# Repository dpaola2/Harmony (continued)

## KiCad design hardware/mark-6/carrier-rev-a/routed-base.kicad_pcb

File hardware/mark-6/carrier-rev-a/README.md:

# Harmony Mark-6 carrier, revision A

Current logistics, September 26: core modules are received, and the revision B shells, LCD supports and carrier gauge passed loose fit checks. Screws and foam are ordered. The SD trial playlist is prepared. The assembled carrier remains unordered. A [supplier quote request](supplier-quote-notes.md) was sent to PCBWay for DFM review and pricing; the response is pending. Physical mating, cable mapping and powered qualification remain open. The historical design record below retains its original dated assumptions.

September 22 display update: **Waveshare 29318 (ST7796S)** replaces unavailable Adafruit #5846. [PiShop.us](https://www.pishop.us/product/3-5inch-capacitive-touch-display-320-480-ips-2tpd/) lists it in stock at $24.95. The [sourcing and compatibility review](display-sourcing.md), [hollow prototype](../../../enclosure/mark-6/fit-prototype/README.md) and [firmware](../../../firmware/mark-6/feather-carrier/README.md) now use this module. The carrier electrical nets are unchanged. Manufacturing remains review-only.

Updated September 22, 2026. HARMONY-17. **Routed prototype design; manufacturing review package, not an order release.**

Dave printed and accepted the **74 x 178 x 28 mm** size dummy. The component
stack now uses the actual Feather and ANO 3D models, specified sockets and
an antenna cutout. The routed four-layer PCB passes KiCad DRC with **zero
violations and zero unconnected nets**. The independent PCB audit matches
122 electrical pads to the schematic and all 28 Feather mating coordinates
to vendor CAD. The schematic also passes ERC.

The [assembly readiness review](assembly-readiness.md) records the corrected ENIG metadata, part/placement audit and the documented U1 thermal-hole DRC warning.

Start with [the design review](output/pdf/design-review.pdf),
[editable PCB](harmony-mark6-carrier.kicad_pcb),
[schematic](harmony-mark6-carrier.kicad_sch), and
[manufacturing review package](output/manufacturing-review/README.md).
[Mechanical review](mechanical-review.md), [power review](power-review.md)
and [machine-readable verification](pcb-verification.json) document the
checks and their limits. No order has been placed.

USB-only operation remains adopted. Battery space is reserved for Mark 8.
The accepted size dummy proves the outside dimensions work for Dave; physical
display fit, header insertion and cable access still require a trial assembly.
The revised prototype uses the Waveshare vendor STEP, including rear connectors.

Dave adopted a 3.5-inch display and separate display/storage buses. The carrier
will arrive assembled, including its sockets and connectors. Dave plugs in a
factory-headered ESP32 Feather V2 (#5900), a display ribbon cable and the
controls cable. No hand soldering is part of the intended assembly.

## Parts and interfaces

Bluetooth verification: the live DigiKey cart contains four Adafruit #5900,
DigiKey 1528-5900-ND. Adafruit's Feather V2 schematic identifies X3 as
ESP32-PICO-MINI-02, containing ESP32-PICO-V3-02. This original ESP32 supports
Bluetooth 4.2 BR/EDR (Classic) and BLE; it meets the radio requirement for
A2DP source streaming. Adafruit #5900 explicitly specifies Classic/LE, and
[Espressif's module datasheet](https://documentation.espressif.com/esp32-pico-mini-02_datasheet_en.html)
confirms BR/EDR. [ESP-IDF's A2DP source example](https://docs.espressif.com/projects/esp-idf/en/stable/esp32/api-reference/bluetooth/esp_a2dp.html)
documents audio transmission. This verifies specifications, not a physical
playback test on the new Feather. Keep this exact Classic-capable model in
the BOM; a BLE-only ESP32-family substitution does not satisfy the requirement.

| Function | Draft implementation | Status |
| --- | --- | --- |
| Processor and Bluetooth | Adafruit ESP32 Feather V2 #5900 in carrier sockets | Four in DigiKey cart; not purchased |
| Display | Waveshare 29318 3.5-inch IPS, via 18-pin ribbon | Glass 61.00 x 92.44 mm; PiShop.us lists in stock |
| Storage | Hirose DM3AT-SF-PEJM5 microSD socket on carrier | Pin and footprint pad sets checked |
| Controls | Previously ordered assembled ANO I2C control board | 50 mm QT-to-QT cable; nominal stack checked |
| Power | USB-C through Feather; TPS62162 3.3 V peripheral supply | USB budget reviewed; physical startup/load/thermal qualification remains |

The EYESPI breakout replaces the proposed FeatherWing connection so that the
carrier can assign display and storage to separate SPI hosts. Its onboard SD
socket stays unused. Capacitive touch on Waveshare 29318 is incidental; the interface
still uses physical controls.

## Proposed GPIO assignment

These are **ESP32 GPIO numbers**, not generic Feather pin numbers. Header
references below use the numbering in Adafruit's Feather V2 Eagle files.
They are for schematic development, not a breadboard wiring instruction.

| Signal | GPIO | Feather header | Destination |
| --- | ---: | --- | --- |
| SD clock | 5 | JP1.6 | Carrier SD CLK |
| SD MOSI | 19 | JP1.5 | Carrier SD CMD |
| SD MISO | 21 | JP1.4 | Carrier SD DAT0 |
| SD select | 25 | JP1.11 | Carrier SD DAT3 |
| Display clock | 14 | JP3.10 | EYESPI 4 |
| Display MOSI | 27 | JP3.6 | EYESPI 5 |
| Display select | 26 | JP1.12 | EYESPI 9 |
| Display command/data | 33 | JP3.7 | EYESPI 7 |
| Display reset | 32 | JP3.9 | EYESPI 8 |
| Display backlight control | 4 | JP1.7 | EYESPI 2 |
| Controls I2C clock | 20 | JP3.11 | Controls SCL |
| Controls I2C data | 22 | JP3.12 | Controls SDA |
| Peripheral power-good input | 34 | JP1.10 | TPS62162 PG |

Use SPI3 for SD and SPI2 for display in native ESP-IDF. The allocation does
not reuse signal GPIOs. A 47k pull-up reinforces GPIO5's normal high boot
strap; the SD clock destination is an input. GPIO12 and GPIO15 stay unused.
Display MISO and touch are unused. The display-side SD select is held high.
The Waveshare display uses SPI without jumper soldering. GPIO34 reads peripheral power-good before firmware starts I/O.

## Power, parts and mechanics

The exact carrier component choices are in `bom-draft.csv`; the grouped
assembler BOM is `output/manufacturing-review/assembly-bom.csv`. Both sockets
and every connector must be fitted by the assembler. F1 is a 0.75 A-hold
Bourns PTC, with 0.52 A hold at 60 C. The regulator uses 2.2 uH and 22 uF
input/output bulk capacitors. The [power review](power-review.md) gives the
source budget, limits and staged first-power procedure.

The [mechanical review](mechanical-review.md) records the 6.5 mm carrier
height, 12 mm ANO spacers, cable orientation and case-port requirements.
The vendor 3D model yields 0.88 mm nominal clearance above the Feather
beneath a 1.6 mm front wall. Display geometry uses the Waveshare vendor STEP.
The detailed assembly is in `output/mechanical/`; it is a review model,
not the final hollow housing.

The carrier cutout removes board material beneath the antenna. Ground pours
avoid the 15 mm halo, while unavoidable header copper remains inside part
of it. The finished device still needs an RF test. Vias inside SMT pads
require filled, copper-capped construction and assembler stencil review.
The release conditions are listed in the manufacturing package.

`build_pcb.py` creates the initial placement; `routing.ses` is the saved
routing result. `routed-base.kicad_pcb` preserves its imported state.
`finish_pcb.py` loads that base, completes the remaining routes, adjusts
edge clearance and fills ground planes. `verify_pcb.py` checks the final
board against the exported schematic netlist. Run it with KiCad's bundled
Python after generating a fresh `final-drc.json`.

## Evidence and limits

Mark-5 SD reads provoked clicks in its local VS1053 analog output; RAM-only
playback was clean. That did not establish shared SPI as the cause. Separate
buses reduce contention; they do not prove clean playback or replace power
layout work. Mark-6 must still demonstrate display refresh during Bluetooth
playback, controls, reconnection and the deferred full-album run.

Vendor Feather, display, ANO and EYESPI CAD, licenses and source hashes are
preserved in `reference/`. Passive socket symbols do not model the ESP32's
electrical limits, so a clean ERC alone cannot establish GPIO compatibility.
The netlist checks explicitly verify the connector mapping and supply
separation; bench and RF tests remain. The previous WROVER wiring is suspended
after two reported board failures; their root cause remains unknown.

## Sources and cross-references

- [Feather V2 vendor CAD](https://github.com/adafruit/Adafruit-ESP32-Feather-V2-PCB)
- [Selected Waveshare 29318 display](https://www.waveshare.com/3.5inch-capacitive-touch-lcd.htm)
- [EYESPI pinout](https://learn.adafruit.com/adafruit-eyespi-breakout-board/pinouts)
- [EYESPI vendor CAD](https://github.com/adafruit/Adafruit-EYESPI-PCB/tree/bc5fa13b55c25feb3bf47e483b4d0bc770fbf20b)
- [TPS62162 datasheet](https://www.ti.com/lit/ds/symlink/tps62160.pdf)
- [Coilcraft XFL4020-222](https://www.coilcraft.com/en-us/products/power/high-voltage-inductors/xfl/xfl4020/xfl4020-222/)
- [Espressif antenna placement guidance](https://documentation.espressif.com/esp-hardware-design-guidelines/en/latest/esp32/index.html)
- [Historical bench wiring](../wiring.md) and [bench evidence](../bench-config.json)
- Work tracking: HARMONY-17; Mark-5 evidence: HARMONY-16.

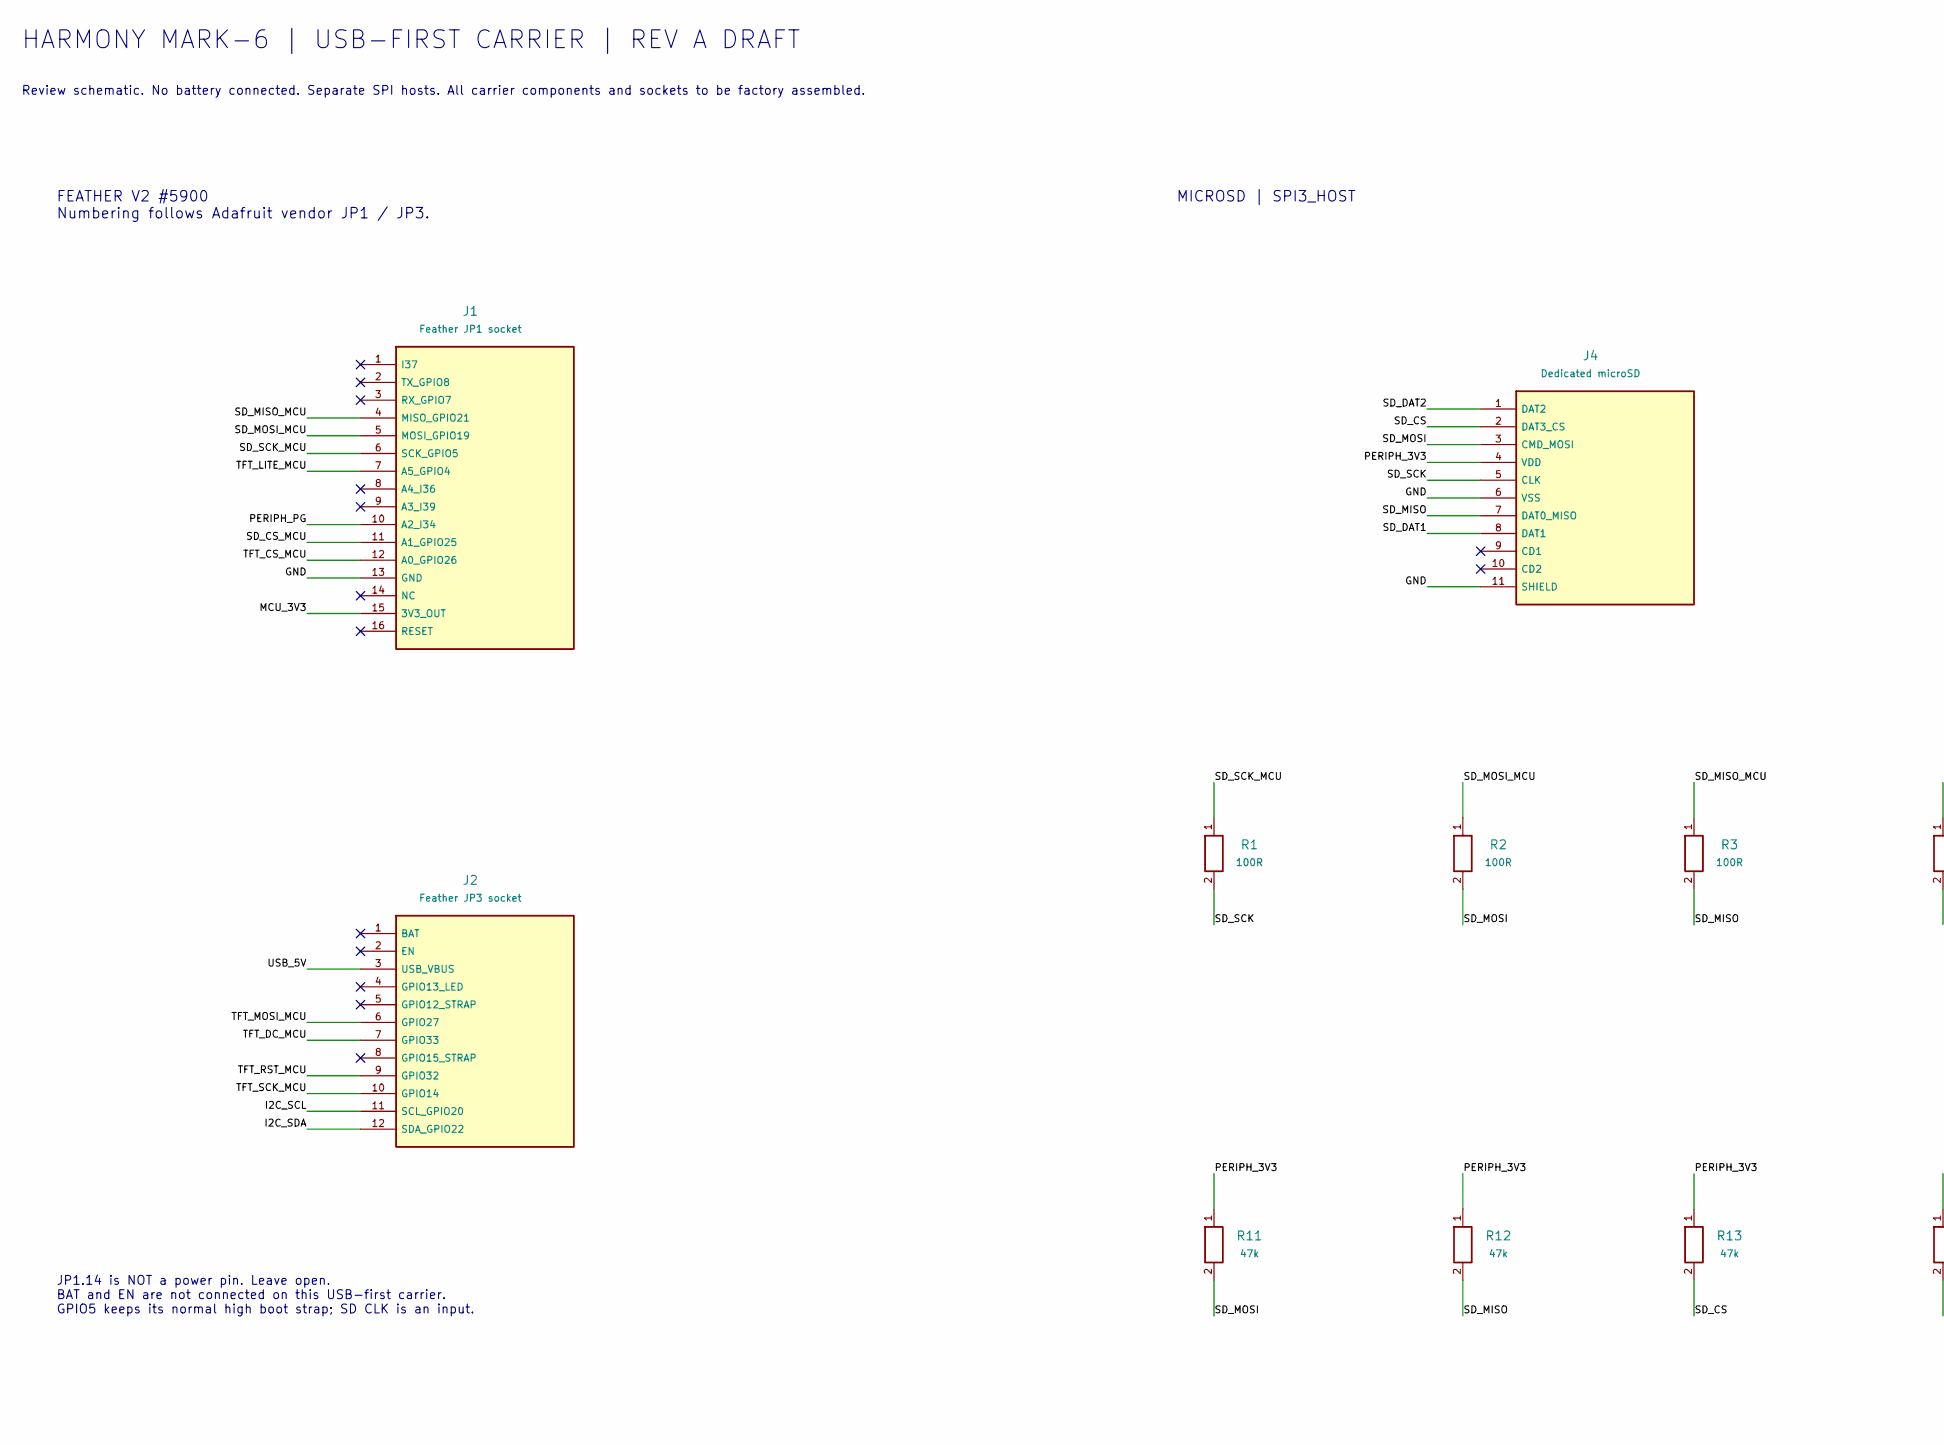
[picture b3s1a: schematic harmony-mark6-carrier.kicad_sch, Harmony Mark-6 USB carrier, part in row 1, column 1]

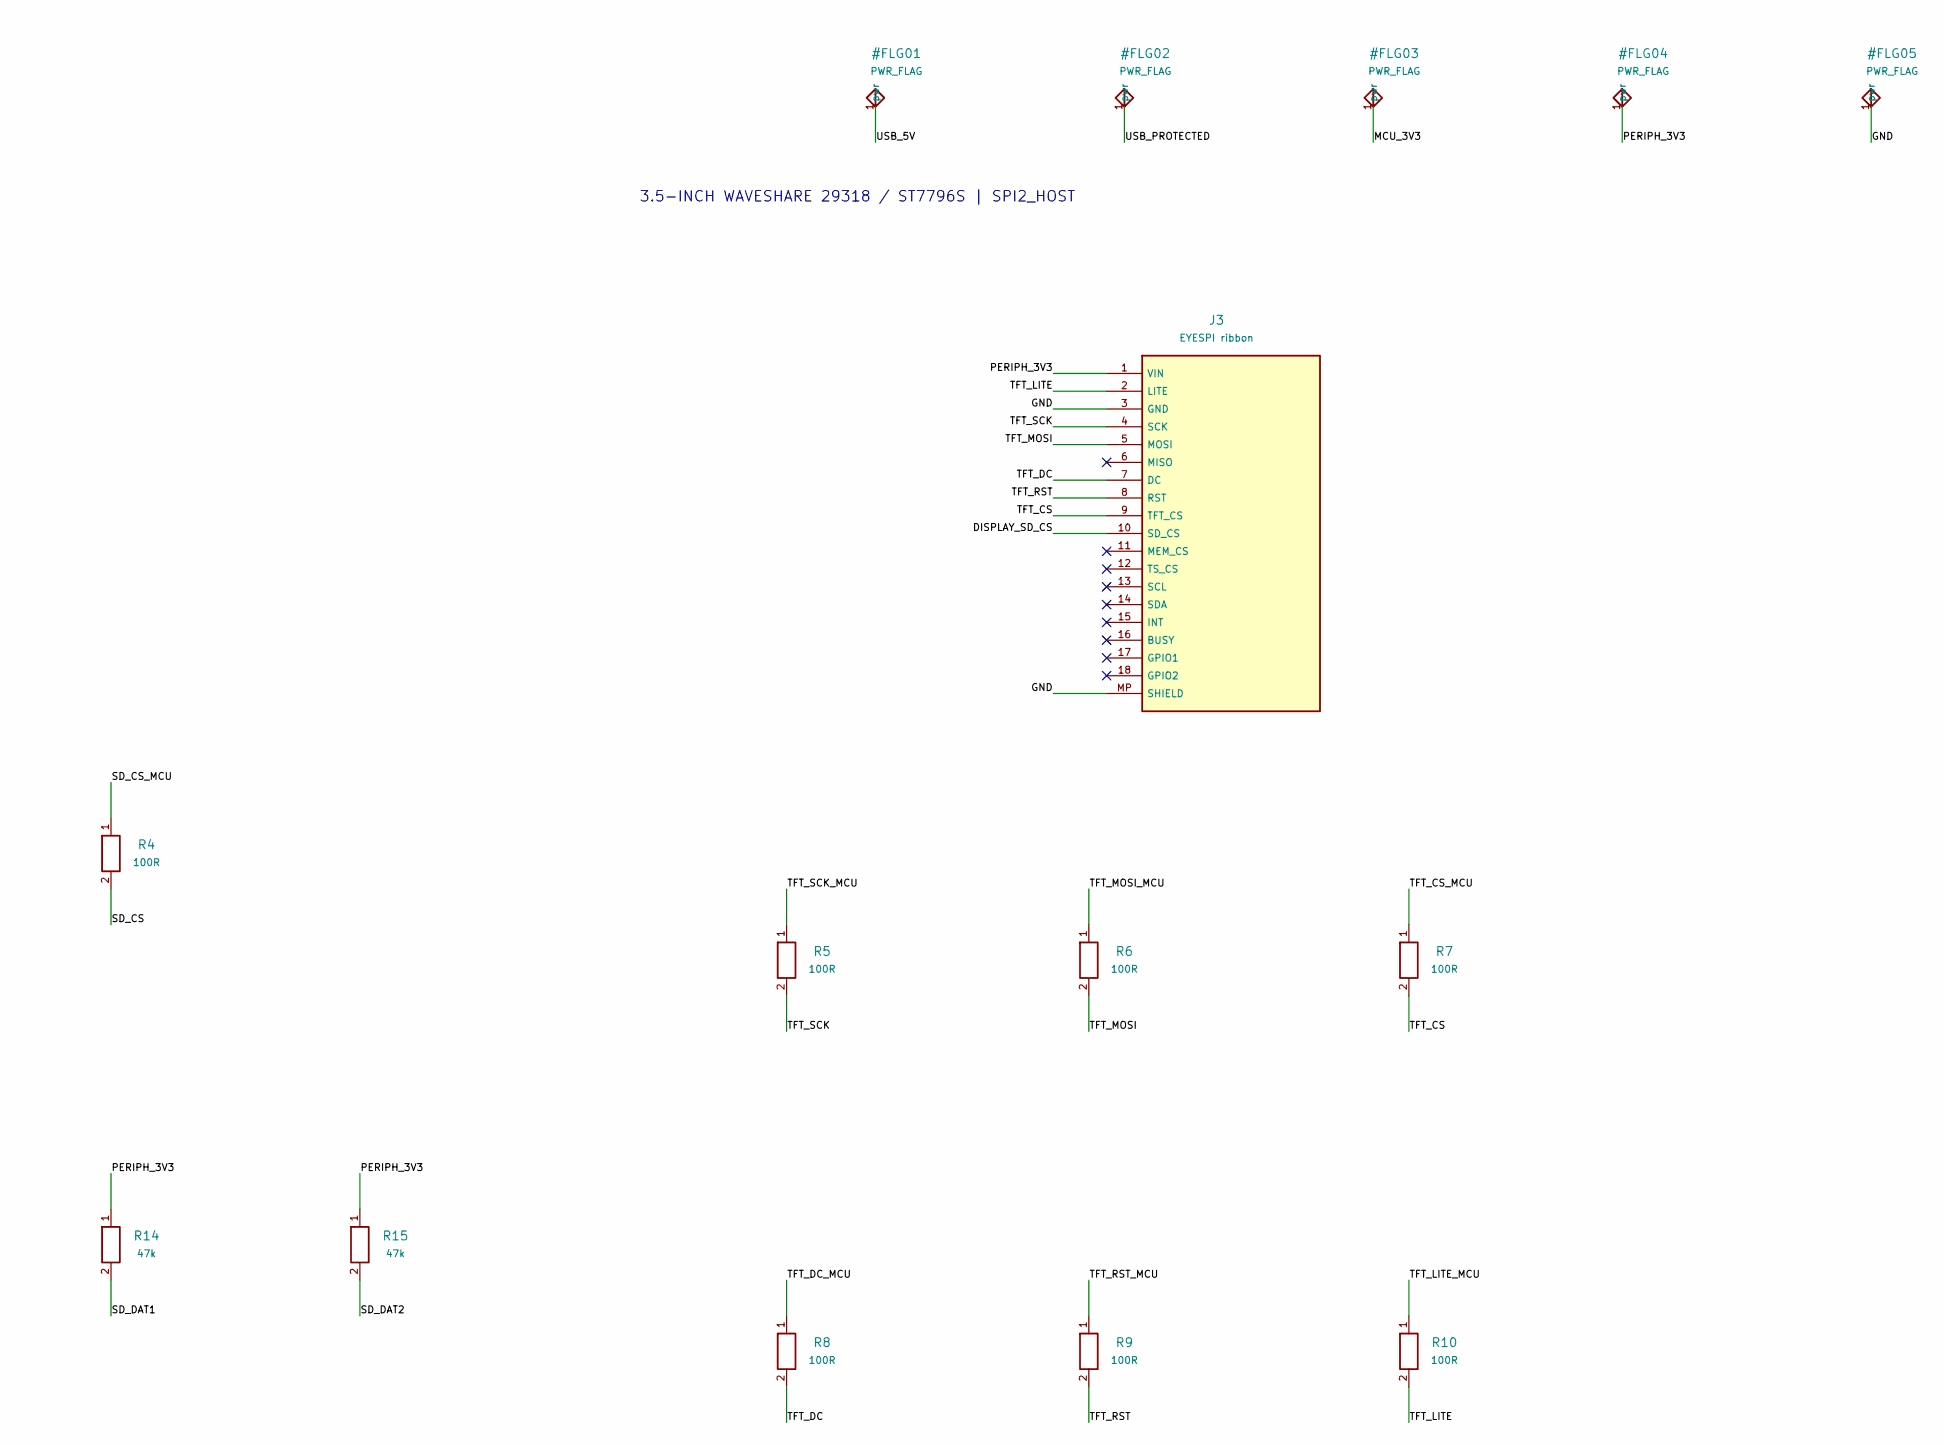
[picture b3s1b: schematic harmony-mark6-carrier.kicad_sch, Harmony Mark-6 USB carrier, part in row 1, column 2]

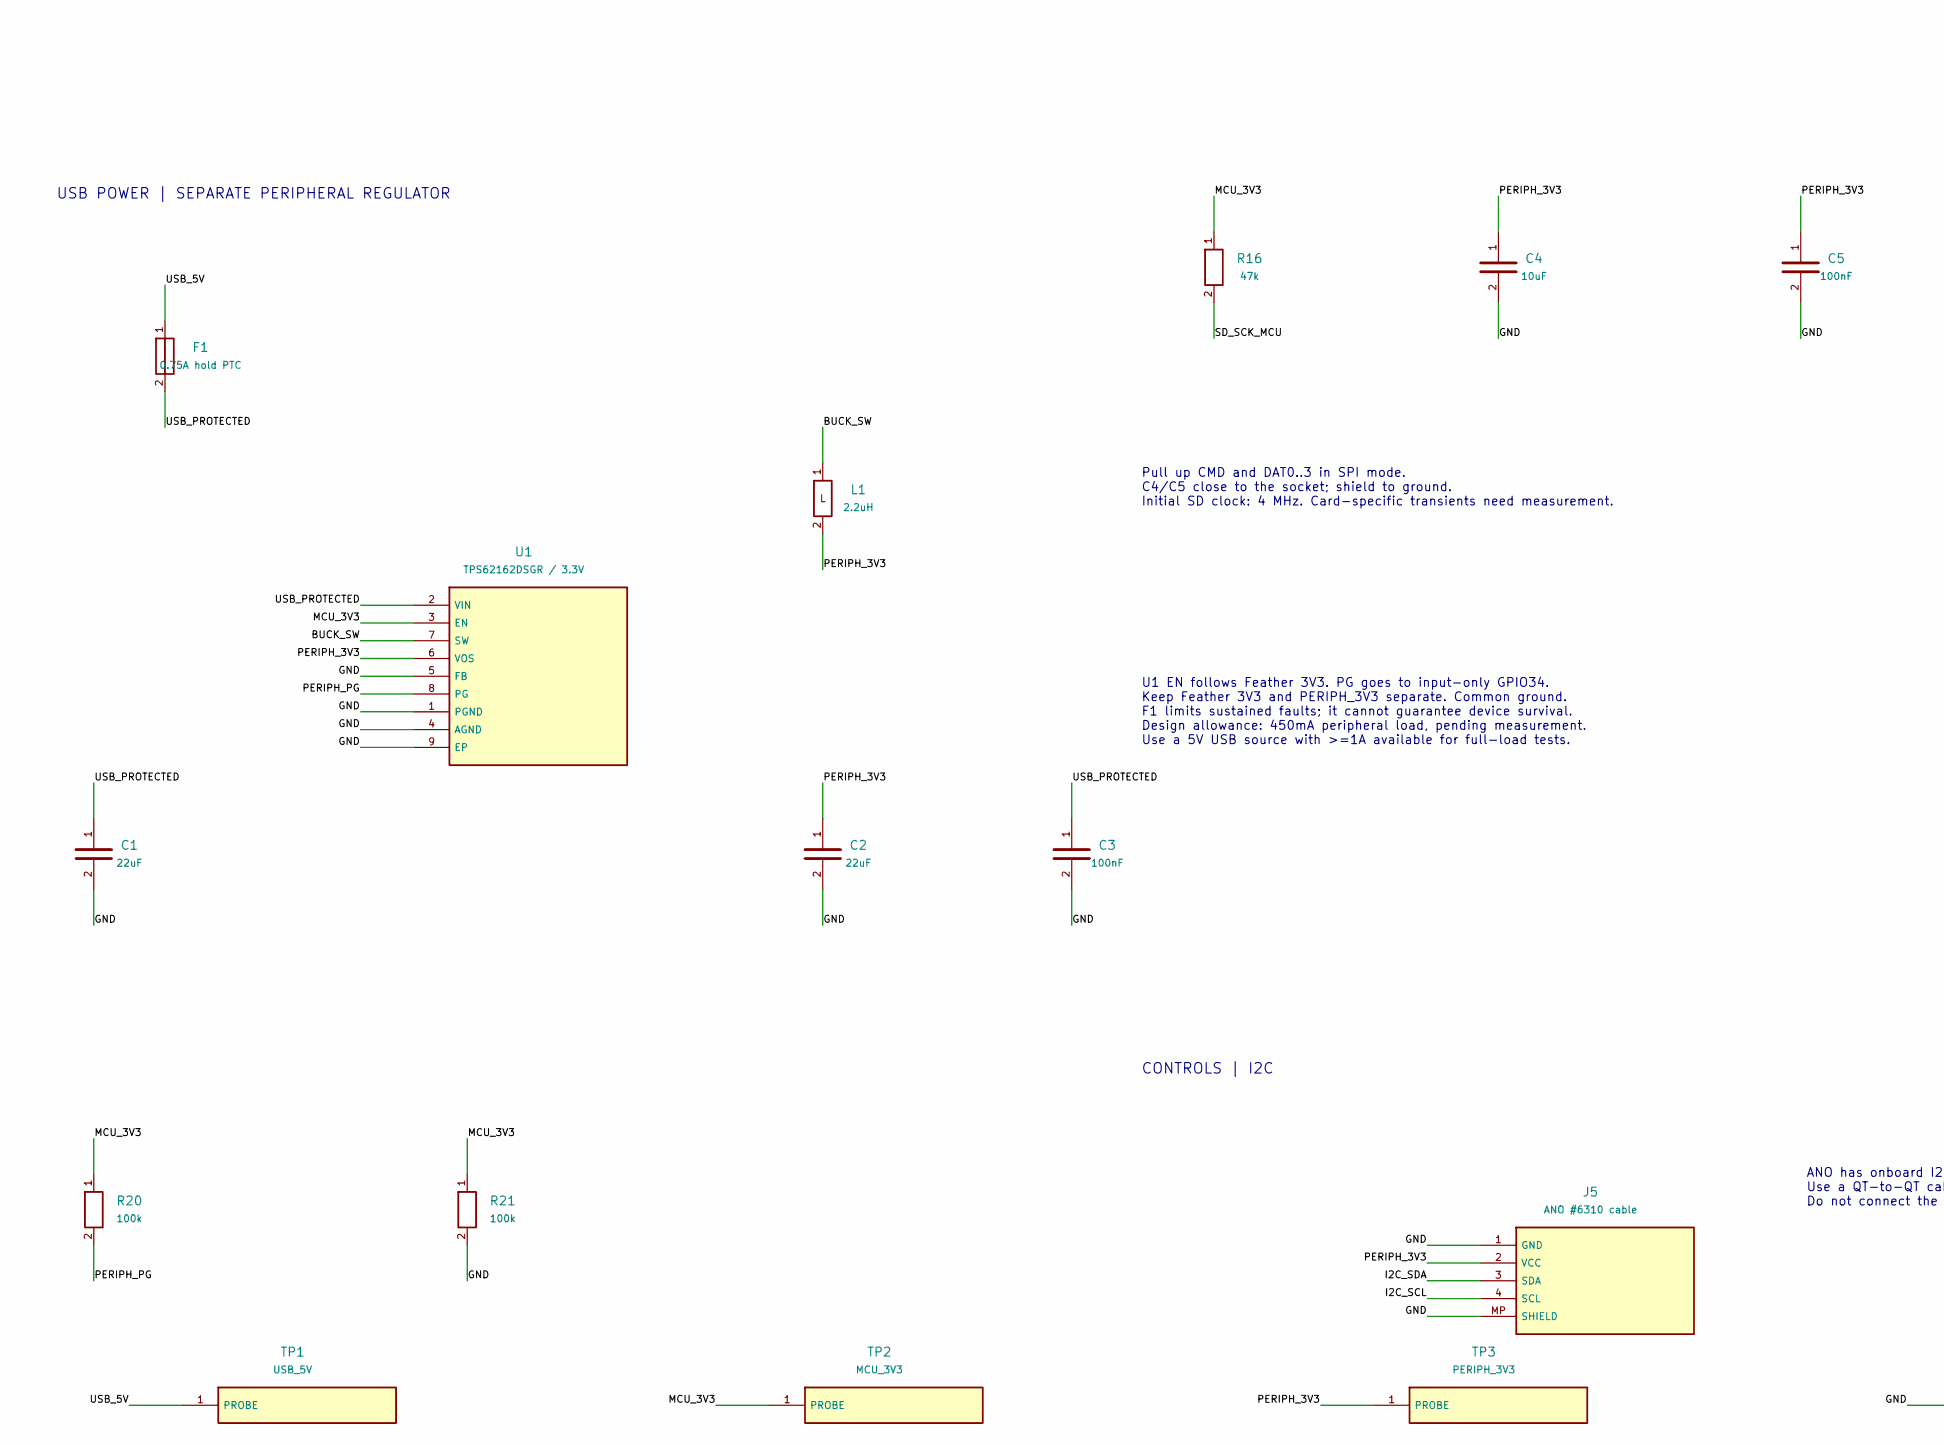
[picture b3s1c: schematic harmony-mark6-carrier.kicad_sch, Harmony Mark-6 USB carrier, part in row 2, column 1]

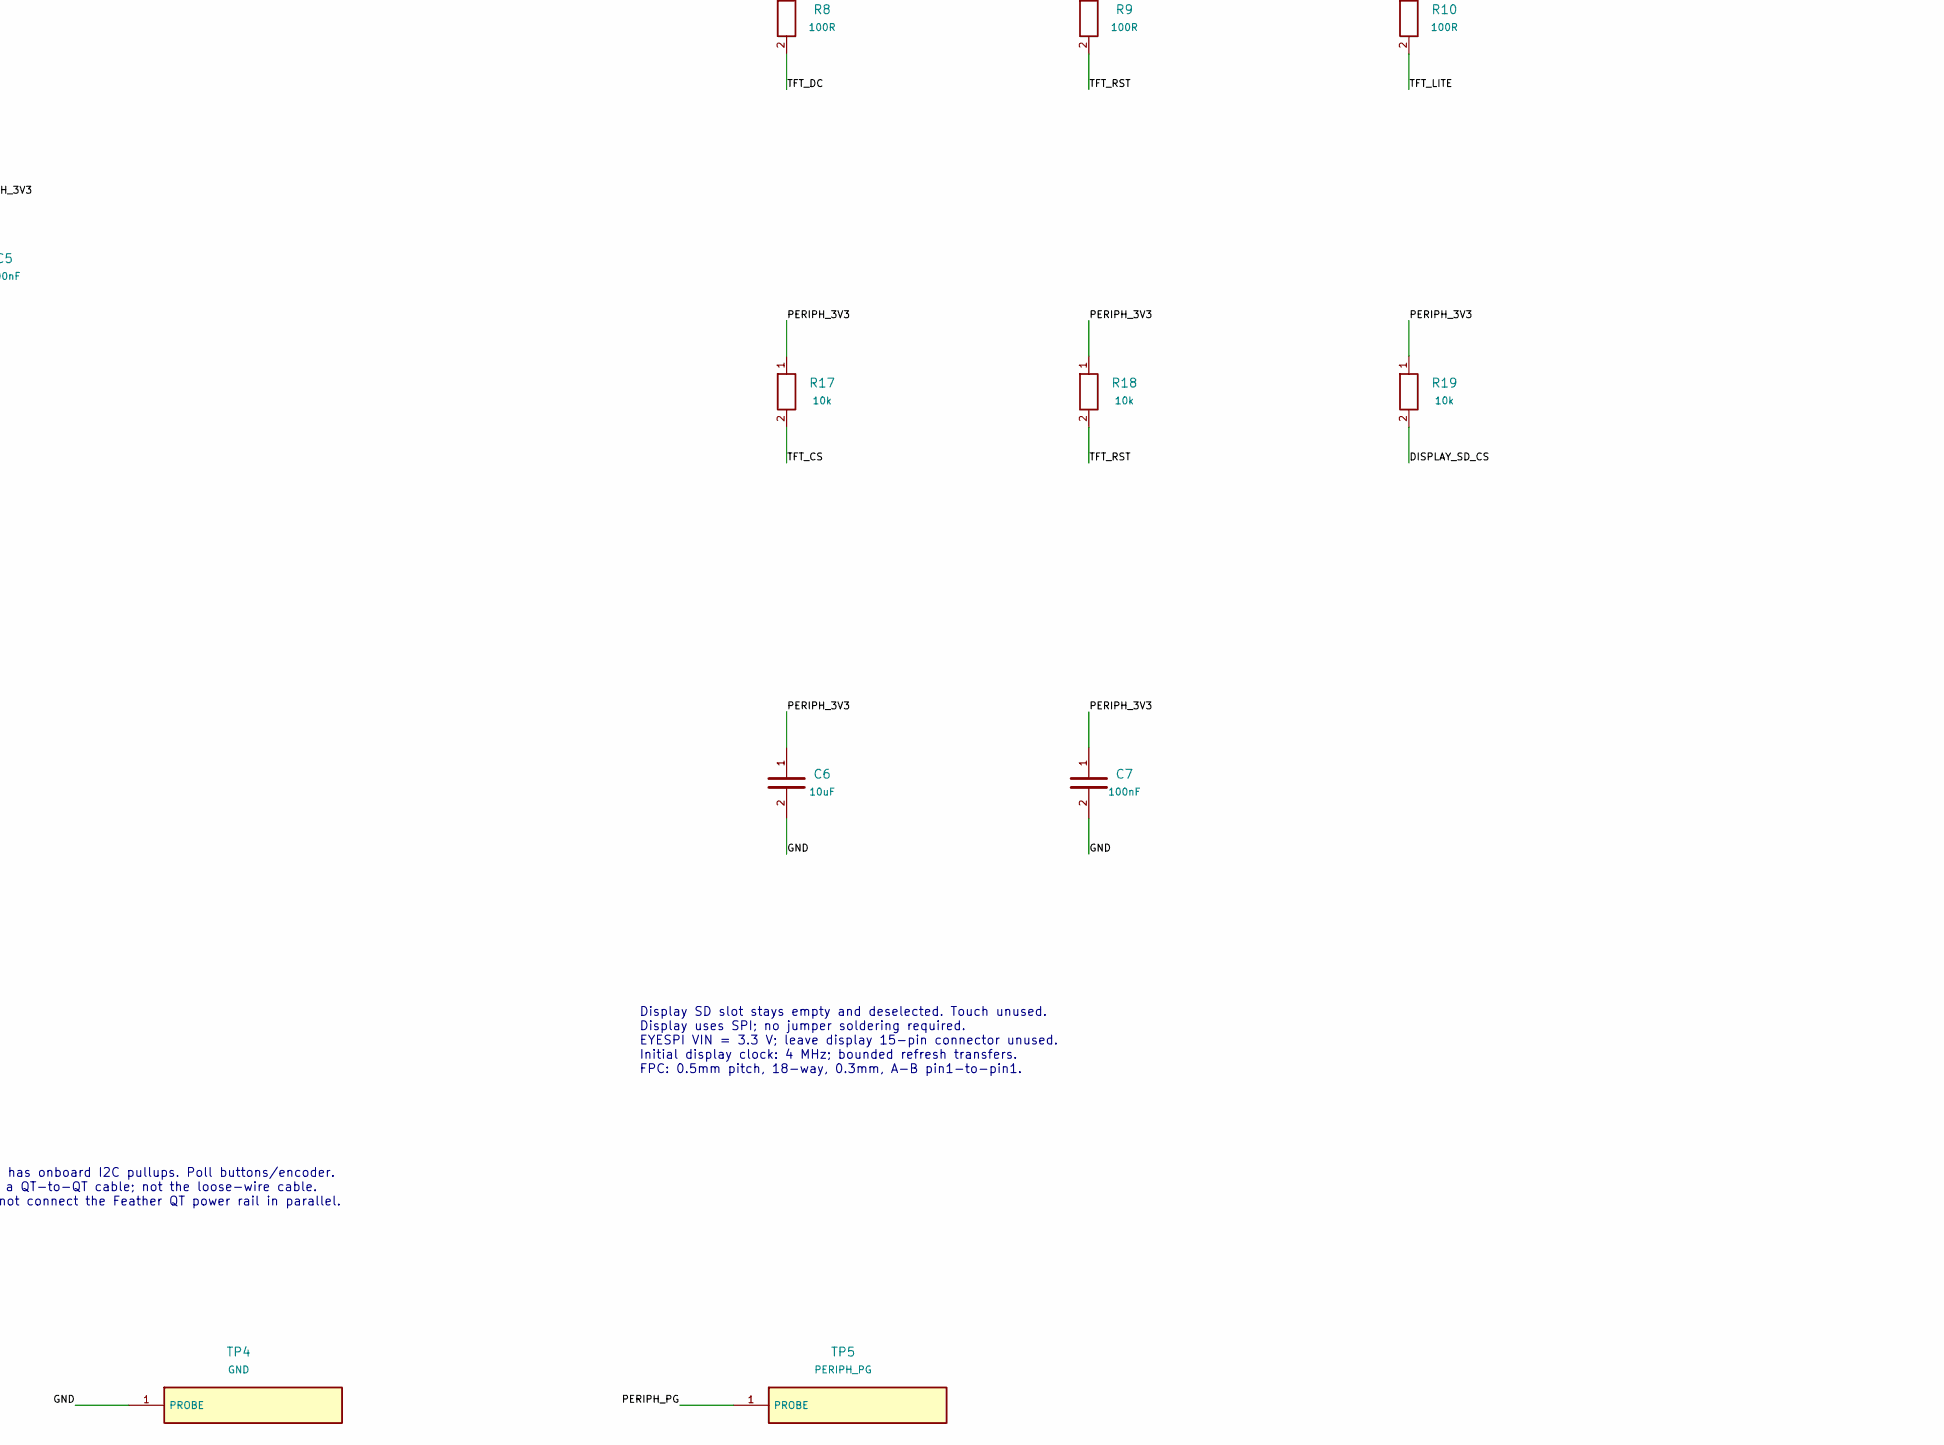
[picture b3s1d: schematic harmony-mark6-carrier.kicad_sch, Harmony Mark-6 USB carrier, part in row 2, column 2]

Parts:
C1, C2: 22uF; C_1210_3225Metric; MPN C3225X7R1C226M250AC
C3, C5, C7: 100nF; C_0805_2012Metric; MPN C0805C104K5RACTU
C4, C6: 10uF; C_0805_2012Metric; MPN C2012X7R1A106K125AC
F1: 0.75A hold PTC; Fuse_1206_3216Metric; MPN MF-NSMF075-2
J1: Feather JP1 socket; PinSocket_1x16_P2.54mm_Vertical; MPN SSW-116-01-G-S
J2: Feather JP3 socket; PinSocket_1x12_P2.54mm_Vertical; MPN SSW-112-01-G-S
J3: EYESPI ribbon; Hirose_FH12-18S-0.5SH_1x18-1MP_P0.50mm_Horizontal; MPN FH12-18S-0.5SH(55)
J4: Dedicated microSD; microSD_HC_Hirose_DM3AT-SF-PEJM5; MPN DM3AT-SF-PEJM5
J5: ANO #6310 cable; JST_SH_SM04B-SRSS-TB_1x04-1MP_P1.00mm_Horizontal; MPN SM04B-SRSS-TB(LF)(SN)
L1: 2.2uH; L_Coilcraft_XxL4020; MPN XFL4020-222MEC
R1, R2, R3, R4, R5, R6, R7, R8, R9, R10: 100R; R_0603_1608Metric; MPN RC0603FR-07100RL
R11, R12, R13, R14, R15, R16: 47k; R_0603_1608Metric; MPN RC0603FR-0747KL
R17, R18, R19: 10k; R_0603_1608Metric; MPN RC0603FR-0710KL
R20, R21: 100k; R_0603_1608Metric; MPN RC0603FR-07100KL
TP1: USB_5V; TestPoint_Pad_D2.0mm
TP2: MCU_3V3; TestPoint_Pad_D2.0mm
TP3: PERIPH_3V3; TestPoint_Pad_D2.0mm
TP4: GND; TestPoint_Pad_D2.0mm
TP5: PERIPH_PG; TestPoint_Pad_D2.0mm
U1: TPS62162DSGR / 3.3V; WSON-8-1EP_2x2mm_P0.5mm_EP0.9x1.6mm_ThermalVias; MPN TPS62162DSGR

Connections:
BUCK_SW: L1.1, U1.7 (SW)
DISPLAY_SD_CS: J3.10 (SD_CS), R19.2
GND: C1.2, C2.2, C3.2, C4.2, C5.2, C6.2, C7.2, J1.13 (GND), J3.3 (GND), J3.MP (SHIELD), J4.6 (VSS), J4.11 (SHIELD), J5.1 (GND), J5.MP (SHIELD), R21.2, TP4.1, U1.1 (PGND), U1.4 (AGND), U1.5 (FB), U1.9 (EP)
I2C_SCL: J2.11 (SCL_GPIO20), J5.4 (SCL)
I2C_SDA: J2.12 (SDA_GPIO22), J5.3 (SDA)
MCU_3V3: J1.15 (3V3_OUT), R16.1, R20.1, R21.1, TP2.1, U1.3 (EN)
PERIPH_3V3: C2.1, C4.1, C5.1, C6.1, C7.1, J3.1 (VIN), J4.4 (VDD), J5.2 (VCC), L1.2, R11.1, R12.1, R13.1, R14.1, R15.1, R17.1, R18.1, R19.1, TP3.1, U1.6 (VOS)
PERIPH_PG: J1.10 (A2_I34), R20.2, TP5.1, U1.8 (PG)
SD_CS: J4.2 (DAT3_CS), R4.2, R13.2
SD_CS_MCU: J1.11 (A1_GPIO25), R4.1
SD_DAT1: J4.8 (DAT1), R14.2
SD_DAT2: J4.1 (DAT2), R15.2
SD_MISO: J4.7 (DAT0_MISO), R3.2, R12.2
SD_MISO_MCU: J1.4 (MISO_GPIO21), R3.1
SD_MOSI: J4.3 (CMD_MOSI), R2.2, R11.2
SD_MOSI_MCU: J1.5 (MOSI_GPIO19), R2.1
SD_SCK: J4.5 (CLK), R1.2
SD_SCK_MCU: J1.6 (SCK_GPIO5), R1.1, R16.2
TFT_CS: J3.9 (TFT_CS), R7.2, R17.2
TFT_CS_MCU: J1.12 (A0_GPIO26), R7.1
TFT_DC: J3.7 (DC), R8.2
TFT_DC_MCU: J2.7 (GPIO33), R8.1
TFT_LITE: J3.2 (LITE), R10.2
TFT_LITE_MCU: J1.7 (A5_GPIO4), R10.1
TFT_MOSI: J3.5 (MOSI), R6.2
TFT_MOSI_MCU: J2.6 (GPIO27), R6.1
TFT_RST: J3.8 (RST), R9.2, R18.2
TFT_RST_MCU: J2.9 (GPIO32), R9.1
TFT_SCK: J3.4 (SCK), R5.2
TFT_SCK_MCU: J2.10 (GPIO14), R5.1
USB_5V: F1.1, J2.3 (USB_VBUS), TP1.1
USB_PROTECTED: C1.1, C3.1, F1.2, U1.2 (VIN)

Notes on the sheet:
HARMONY MARK-6 | USB-FIRST CARRIER | REV A DRAFT
Review schematic. No battery connected. Separate SPI hosts. All carrier components and sockets to be factory assembled.
FEATHER V2 #5900 Numbering follows Adafruit vendor JP1 / JP3.
JP1.14 is NOT a power pin. Leave open. BAT and EN are not connected on this USB-first carrier. GPIO5 keeps its normal high boot strap; SD CLK is an input.
MICROSD | SPI3_HOST
Pull up CMD and DAT0..3 in SPI mode. C4/C5 close to the socket; shield to ground. Initial SD clock: 4 MHz. Card-specific transients need measurement.
3.5-INCH WAVESHARE 29318 / ST7796S | SPI2_HOST
Display SD slot stays empty and deselected. Touch unused. Display uses SPI; no jumper soldering required. EYESPI VIN = 3.3 V; leave display 15-pin connector unused. Initial display clock: 4 MHz; bounded refresh transfers. FPC: 0.5mm pitch, 18-way, 0.3mm, A-B pin1-to-pin1.
USB POWER | SEPARATE PERIPHERAL REGULATOR
U1 EN follows Feather 3V3. PG goes to input-only GPIO34. Keep Feather 3V3 and PERIPH_3V3 separate. Common ground. F1 limits sustained faults; it cannot guarantee device survival. Design allowance: 450mA peripheral load, pending measurement. Use a 5V USB source with >=1A available for full-load test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
CONTROLS | I2C
ANO has onboard I2C pullups. Poll buttons/encoder. Use a QT-to-QT cable; not the loose-wire cable. Do not connect the Feather QT power rail in parallel.

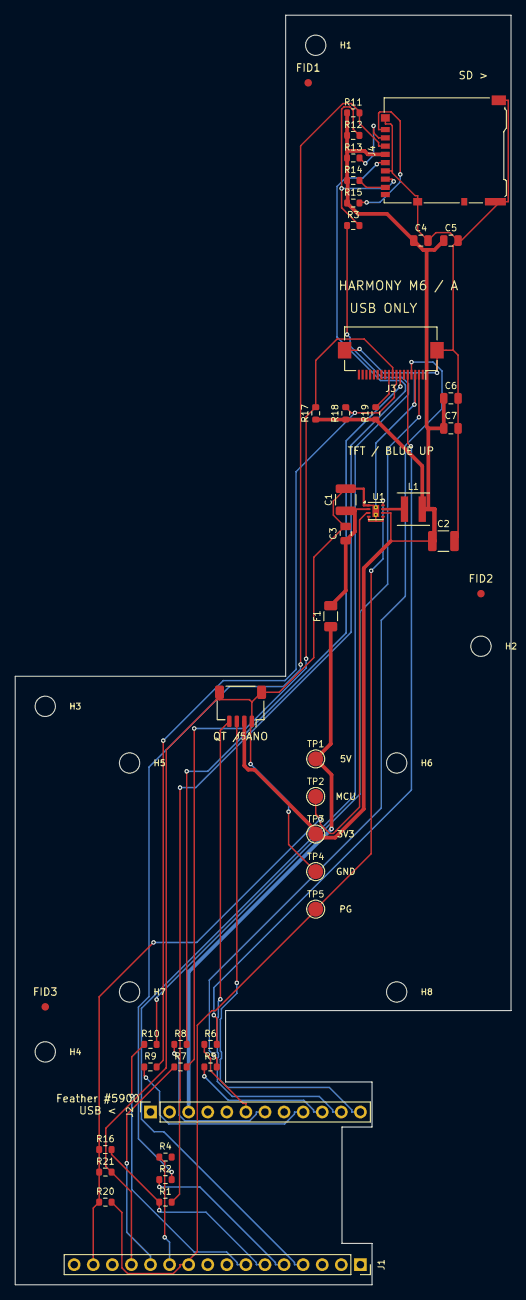
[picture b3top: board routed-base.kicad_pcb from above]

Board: 4 copper layers, 66.0 x 169.0 mm, 52 parts (0 on the bottom side), 32 nets.

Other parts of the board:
FID1, FID2, FID3: Fiducial_1mm_Mask2mm
H1, H2, H3, H4, H5, H6, H7, H8: MountingHole_2.7mm_M2.5

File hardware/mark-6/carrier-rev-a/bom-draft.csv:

ref,value,mpn,footprint,note
J1,Feather JP1 socket,SSW-116-01-G-S,Connector_PinSocket_2.54mm:PinSocket_1x16_P2.54mm_Vertical,"Factory-installed Samtec socket: 8.51mm body, 2.64mm solder tails; vendor top-view coordinates"
J2,Feather JP3 socket,SSW-112-01-G-S,Connector_PinSocket_2.54mm:PinSocket_1x12_P2.54mm_Vertical,"Factory-installed Samtec socket: 8.51mm body, 2.64mm solder tails; vendor top-view coordinates"
J4,Dedicated microSD,DM3AT-SF-PEJM5,Connector_Card:microSD_HC_Hirose_DM3AT-SF-PEJM5,"Pins 9/10 are unused card-detect contacts. Pin 11 is shield, including all four mounting tabs."
R1,100R,RC0603FR-07100RL,Resistor_SMD:R_0603_1608Metric,"Yageo RC series, 1%, 0.1W, 0603"
R2,100R,RC0603FR-07100RL,Resistor_SMD:R_0603_1608Metric,"Yageo RC series, 1%, 0.1W, 0603"
R3,100R,RC0603FR-07100RL,Resistor_SMD:R_0603_1608Metric,"Yageo RC series, 1%, 0.1W, 0603"
R4,100R,RC0603FR-07100RL,Resistor_SMD:R_0603_1608Metric,"Yageo RC series, 1%, 0.1W, 0603"
R11,47k,RC0603FR-0747KL,Resistor_SMD:R_0603_1608Metric,"Yageo RC series, 1%, 0.1W, 0603"
R12,47k,RC0603FR-0747KL,Resistor_SMD:R_0603_1608Metric,"Yageo RC series, 1%, 0.1W, 0603"
R13,47k,RC0603FR-0747KL,Resistor_SMD:R_0603_1608Metric,"Yageo RC series, 1%, 0.1W, 0603"
R14,47k,RC0603FR-0747KL,Resistor_SMD:R_0603_1608Metric,"Yageo RC series, 1%, 0.1W, 0603"
R15,47k,RC0603FR-0747KL,Resistor_SMD:R_0603_1608Metric,"Yageo RC series, 1%, 0.1W, 0603"
R16,47k,RC0603FR-0747KL,Resistor_SMD:R_0603_1608Metric,"Yageo RC series, 1%, 0.1W, 0603"
C4,10uF,C2012X7R1A106K125AC,Capacitor_SMD:C_0805_2012Metric,"X7R; C1/C2 22uF 16V +/-20% 1210, C4/C6 10uF 10V, 100nF 50V. See power-review.md for bias/temperature budget"
C5,100nF,C0805C104K5RACTU,Capacitor_SMD:C_0805_2012Metric,"X7R; C1/C2 22uF 16V +/-20% 1210, C4/C6 10uF 10V, 100nF 50V. See power-review.md for bias/temperature budget"
J3,EYESPI ribbon,FH12-18S-0.5SH(55),Connector_FFC-FPC:Hirose_FH12-18S-0.5SH_1x18-1MP_P0.50mm_Horizontal,"Bottom contact, 0.3mm FPC, 0.5mm pitch; Adafruit #5239 A-B cable maps 1 to 1. Copper faces board; blue stiffener outward"
R5,100R,RC0603FR-07100RL,Resistor_SMD:R_0603_1608Metric,"Yageo RC series, 1%, 0.1W, 0603"
R6,100R,RC0603FR-07100RL,Resistor_SMD:R_0603_1608Metric,"Yageo RC series, 1%, 0.1W, 0603"
R7,100R,RC0603FR-07100RL,Resistor_SMD:R_0603_1608Metric,"Yageo RC series, 1%, 0.1W, 0603"
R8,100R,RC0603FR-07100RL,Resistor_SMD:R_0603_1608Metric,"Yageo RC series, 1%, 0.1W, 0603"
R9,100R,RC0603FR-07100RL,Resistor_SMD:R_0603_1608Metric,"Yageo RC series, 1%, 0.1W, 0603"
R10,100R,RC0603FR-07100RL,Resistor_SMD:R_0603_1608Metric,"Yageo RC series, 1%, 0.1W, 0603"
R17,10k,RC0603FR-0710KL,Resistor_SMD:R_0603_1608Metric,"Yageo RC series, 1%, 0.1W, 0603"
R18,10k,RC0603FR-0710KL,Resistor_SMD:R_0603_1608Metric,"Yageo RC series, 1%, 0.1W, 0603"
R19,10k,RC0603FR-0710KL,Resistor_SMD:R_0603_1608Metric,"Yageo RC series, 1%, 0.1W, 0603"
C6,10uF,C2012X7R1A106K125AC,Capacitor_SMD:C_0805_2012Metric,"X7R; C1/C2 22uF 16V +/-20% 1210, C4/C6 10uF 10V, 100nF 50V. See power-review.md for bias/temperature budget"
C7,100nF,C0805C104K5RACTU,Capacitor_SMD:C_0805_2012Metric,"X7R; C1/C2 22uF 16V +/-20% 1210, C4/C6 10uF 10V, 100nF 50V. See power-review.md for bias/temperature budget"
F1,0.75A hold PTC,MF-NSMF075-2,Fuse:Fuse_1206_3216Metric,"Bourns 1206, 6V, 0.75A hold at 23C; 0.52A at 60C; 1.5A trip at 23C. Peripheral branch only; not GPIO protection"
U1,TPS62162DSGR / 3.3V,TPS62162DSGR,Package_SON:WSON-8-1EP_2x2mm_P0.5mm_EP0.9x1.6mm_ThermalVias,
L1,2.2uH,XFL4020-222MEC,Inductor_SMD:L_Coilcraft_XxL4020,"2.2uH shielded; Coilcraft XFL4020 series. 4.0 x 4.0mm body, 2.2mm maximum height; shielded"
C1,22uF,C3225X7R1C226M250AC,Capacitor_SMD:C_1210_3225Metric,"X7R; C1/C2 22uF 16V +/-20% 1210, C4/C6 10uF 10V, 100nF 50V. See power-review.md for bias/temperature budget"
C2,22uF,C3225X7R1C226M250AC,Capacitor_SMD:C_1210_3225Metric,"X7R; C1/C2 22uF 16V +/-20% 1210, C4/C6 10uF 10V, 100nF 50V. See power-review.md for bias/temperature budget"
C3,100nF,C0805C104K5RACTU,Capacitor_SMD:C_0805_2012Metric,"X7R; C1/C2 22uF 16V +/-20% 1210, C4/C6 10uF 10V, 100nF 50V. See power-review.md for bias/temperature budget"
R20,100k,RC0603FR-07100KL,Resistor_SMD:R_0603_1608Metric,"Yageo RC series, 1%, 0.1W, 0603"
R21,100k,RC0603FR-07100KL,Resistor_SMD:R_0603_1608Metric,"Yageo RC series, 1%, 0.1W, 0603"
J5,ANO #6310 cable,SM04B-SRSS-TB(LF)(SN),Connector_JST:JST_SH_SM04B-SRSS-TB_1x04-1MP_P1.00mm_Horizontal,
TP1,USB_5V,,TestPoint:TestPoint_Pad_D2.0mm,Bare PCB probe pad; no assembly component
TP2,MCU_3V3,,TestPoint:TestPoint_Pad_D2.0mm,Bare PCB probe pad; no assembly component
TP3,PERIPH_3V3,,TestPoint:TestPoint_Pad_D2.0mm,Bare PCB probe pad; no assembly component
TP4,GND,,TestPoint:TestPoint_Pad_D2.0mm,Bare PCB probe pad; no assembly component
TP5,PERIPH_PG,,TestPoint:TestPoint_Pad_D2.0mm,Bare PCB probe pad; no assembly component

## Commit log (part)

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2025-11-22 project overview and plan files
2025-11-22 agents
2025-11-22 tasks
2025-11-22 CS1: stubs, docs
2025-11-22 CS3 gameplan
2025-11-22 CS4: tests
2025-11-22 CS5 gameplan
2025-11-22 CS5 first pass
2025-11-22 updated navigation spec
2025-11-22 updated navigation menu implementation
2025-11-22 update spec for album/artist/track number etc
2025-11-22 Implemented CS5.5 hierarchical library with drilldown and optional PC directory loading.
    - Core navigation refactor: core/player_app.py now drives a Library → Artists → Albums → Tracks drilldown, with per-level selection, back/left stepping up, track selection starting
    playback and auto-jumping to Now Playing, and play/pause within track lists. Added root-aware highlighting updates and safer handling of unknown metadata.
    - Library indexing: new core/library.py builds artist/album indexes with fallback “Unknown” labels and stable track sorting.
    - Models updated: Track now carries artist, album, track_number (optional), and PlayerState tracks root/library selection levels.
2025-11-22 impelment artist/album in navigation
2025-11-22 volume controls
2025-11-22 hardware notes and updated task list
2025-11-22 prototype hardware dev board details
2025-11-22 split prototype phases to use wroom for now, wrover when it arrives, etc
2025-11-22 clean up TASKS.md
2025-11-22 hardware docs
2025-11-22 sd card docs
2025-11-22 prototype 1 hardware task list
2025-11-22 first wiring diagram
2025-11-22 update for waveshare idiosyncrasy
2025-11-22 update agents
2025-11-23 flashing instructions and micropython binary
2025-11-23 display test works, sd card paused
2025-11-23 gameplan for UI
2025-11-23 display works
2025-11-23 update color scheme
2025-11-23 gameplan for upgraded UI
2025-11-23 splash images + simple loading screen
2025-11-23 text color
2025-11-23 fix offset issue
2025-11-23 documentation
